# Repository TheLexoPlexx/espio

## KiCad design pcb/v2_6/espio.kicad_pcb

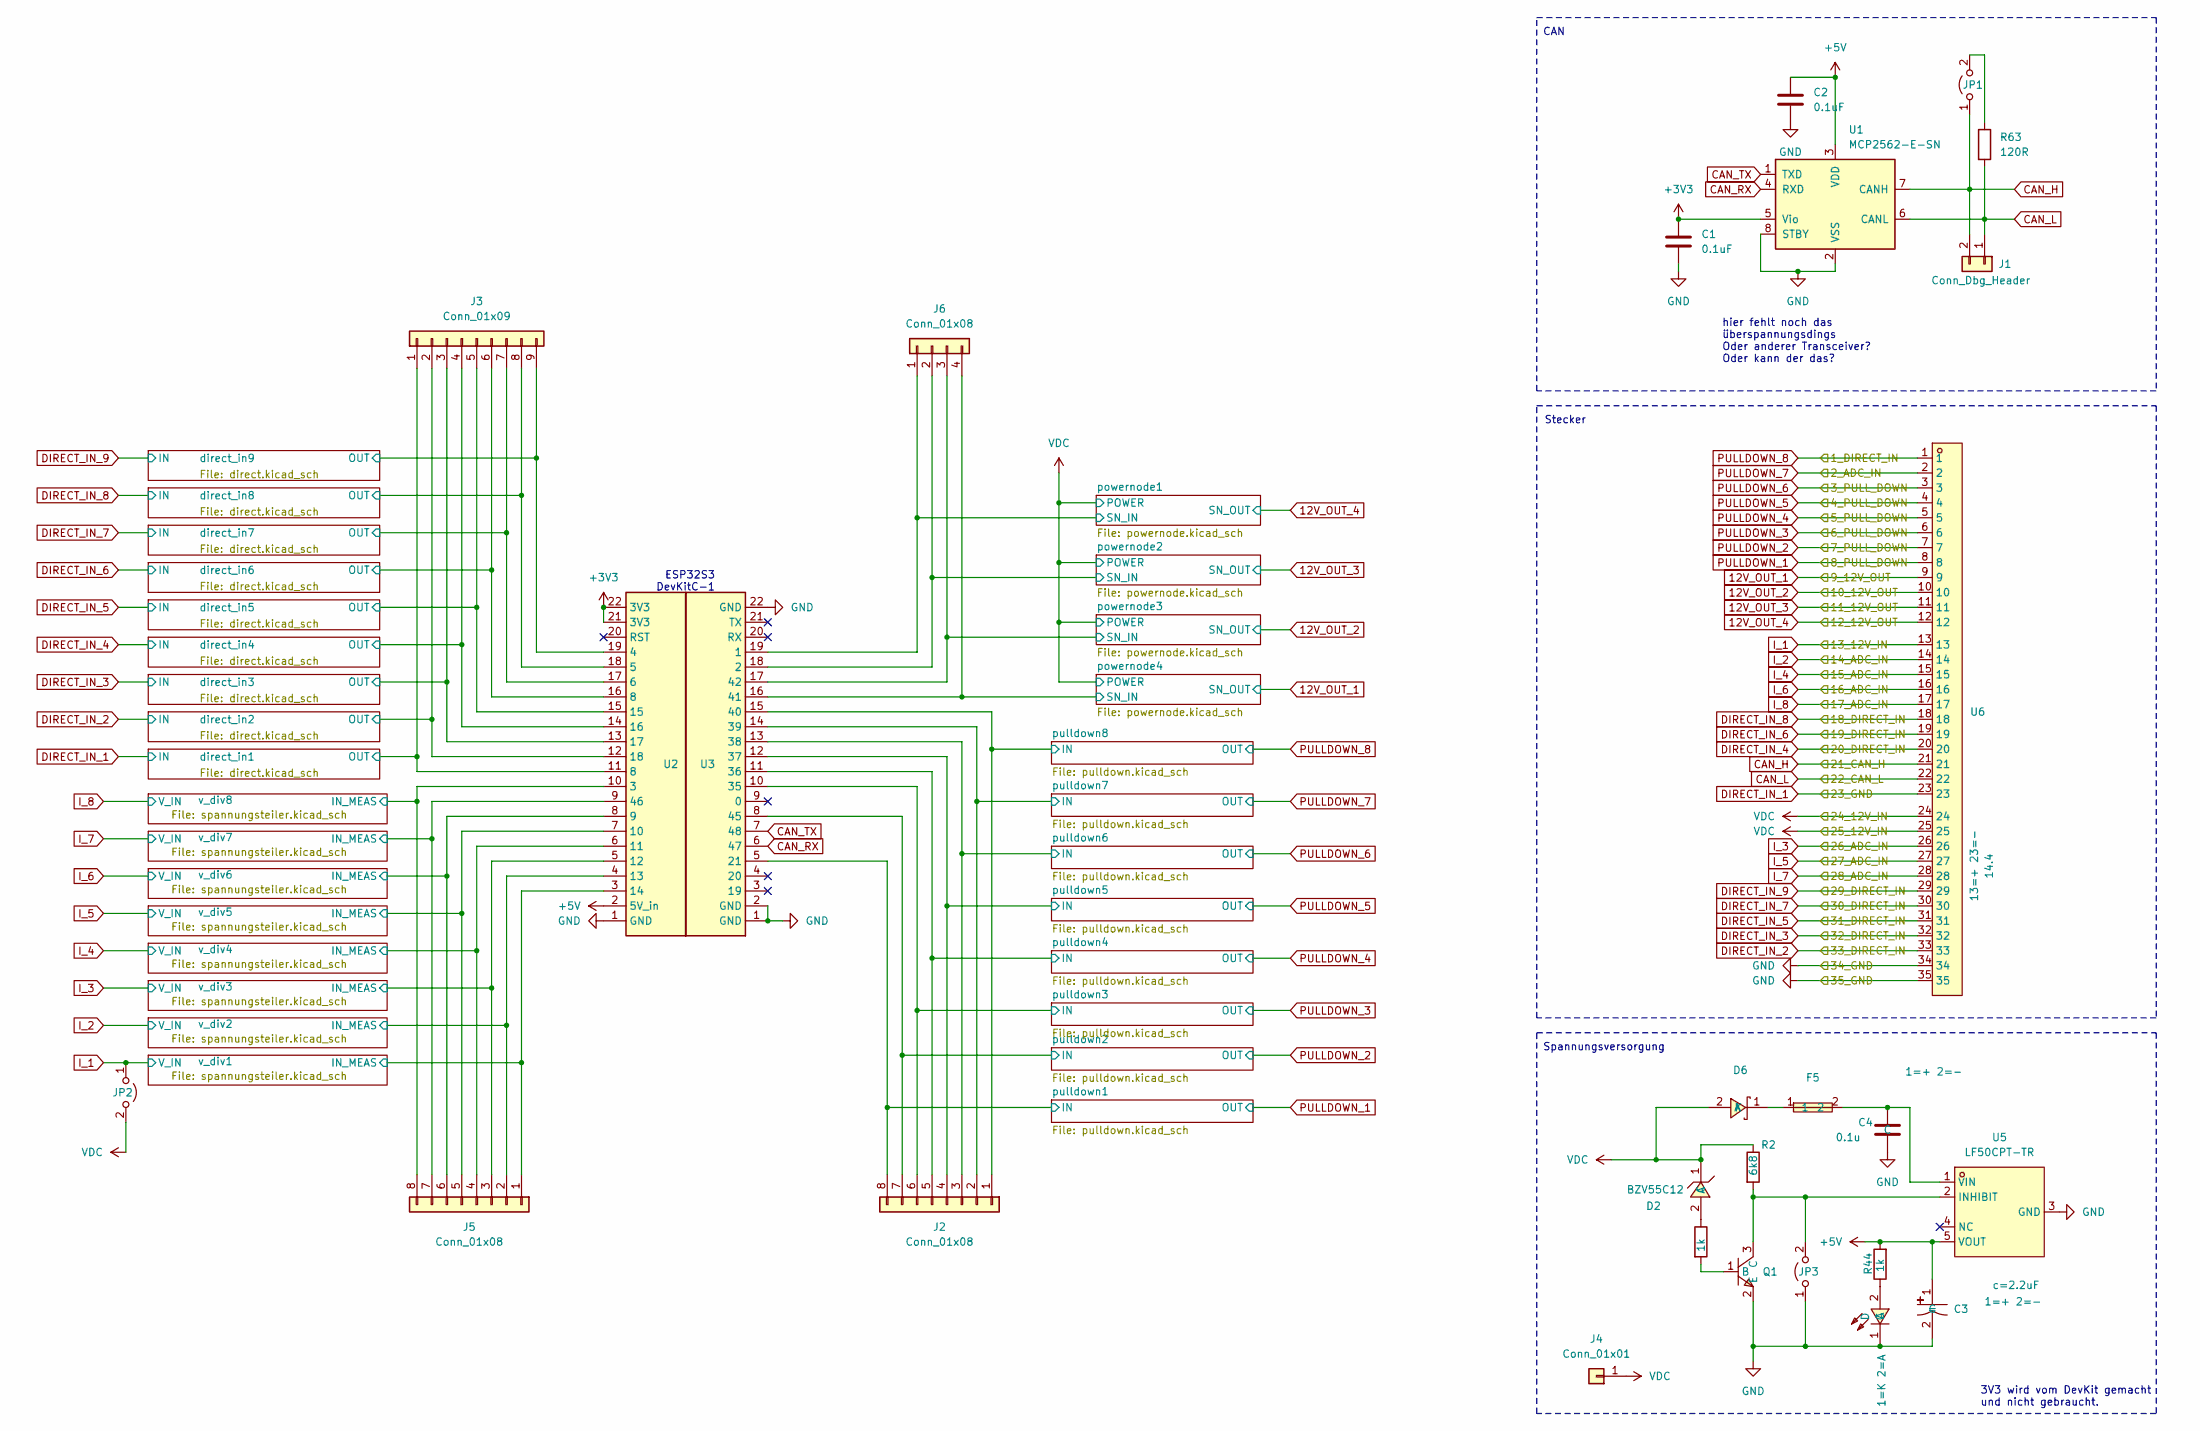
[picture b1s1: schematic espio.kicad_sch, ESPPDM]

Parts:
C1, C2: 0.1uF; C_0603_1608Metric
C3: c=2.2uF; CAP-SMD_BD6.3-L6.6-W6.6-FD; LCSC Part C335981
C4: 0.1u; C_0603_1608Metric
D2: BZV55C12; SOD-80_L3.5-W1.5-RD; LCSC Part C545360
D6: 1N5819HW-7-F; SOD-123_L2.7-W1.6-LS3.7-RD; LCSC Part C82544
F5: 1812L050/30PR; F1812; LCSC Part C151168
J1: Conn_Dbg_Header; PinHeader_1x02_P2.54mm_Vertical
J2, J5: Conn_01x08; PinHeader_1x08_P2.54mm_Vertical
J3: Conn_01x09; PinHeader_1x09_P2.54mm_Vertical
J4: Conn_01x01; PinHeader_1x01_P2.54mm_Vertical
J6: Conn_01x08; PinHeader_1x04_P2.54mm_Vertical
JP1, JP3: Jumper_2_Open; SolderJumper-2_P1.3mm_Open_Pad1.0x1.5mm
JP2: VCC_as_Pin_8; SolderJumper-2_P1.3mm_Open_Pad1.0x1.5mm
LED1: ${SIM.PARAMS}; LED0603-RD; LCSC Part C193191
Q1: 2SC1623 300-400; SOT-23-3_L2.9-W1.3-P1.90-LS2.4-BR; LCSC Part C2133
R2: 6k8; R_0603_1608Metric
R3, R44: 1k; R_0603_1608Metric
R63: 120R; R_0603_1608Metric
U1: MCP2562-E-SN; SOIC-8_3.9x4.9mm_P1.27mm; lcsc C53609
U2, U3: PinSocket_1x22_P2.54mm_Vertical
U5: LF50CPT-TR; PPAK-5_L6.5-W6.1-P1.27-LS10.0-TL; LCSC Part C2970955
U6: 14.4; CONN-TH_35P-P4.00_K776180WR-2; LCSC Part C2997462

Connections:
12V_OUT_1: U6.9; also elsewhere on the board
12V_OUT_2: U6.10; also elsewhere on the board
12V_OUT_3: U6.11; also elsewhere on the board
12V_OUT_4: U6.12; also elsewhere on the board
+3V3: C1.1, U1.5 (Vio), U2.21 (3V3), U2.22 (3V3)
+5V: C2.1, C3.1, R44.2, U1.3 (VDD), U2.2 (5V_in), U5.5 (VOUT)
/powernode1/SN_IN: J6.1, U3.19 (1); also elsewhere on the board
/powernode2/SN_IN: J6.2, U3.18 (2); also elsewhere on the board
/powernode3/SN_IN: J6.3, U3.17 (42); also elsewhere on the board
/powernode4/SN_IN: J6.4, U3.16 (41); also elsewhere on the board
/pulldown1/IN: J2.8, U3.5 (21); also elsewhere on the board
/pulldown2/IN: J2.7, U3.8 (45); also elsewhere on the board
/pulldown3/IN: J2.6, U3.10 (35); also elsewhere on the board
/pulldown4/IN: J2.5, U3.11 (36); also elsewhere on the board
/pulldown5/IN: J2.4, U3.12 (37); also elsewhere on the board
/pulldown6/IN: J2.3, U3.13 (38); also elsewhere on the board
/pulldown7/IN: J2.2, U3.14 (39); also elsewhere on the board
/pulldown8/IN: J2.1, U3.15 (40); also elsewhere on the board
/v_div1/IN_MEAS: J5.1, U2.3 (14); also elsewhere on the board
/v_div2/IN_MEAS: J5.2, U2.4 (13); also elsewhere on the board
/v_div3/IN_MEAS: J5.3, U2.5 (12); also elsewhere on the board
/v_div4/IN_MEAS: J5.4, U2.6 (11); also elsewhere on the board
/v_div5/IN_MEAS: J5.5, U2.7 (10); also elsewhere on the board
/v_div6/IN_MEAS: J5.6, U2.8 (9); also elsewhere on the board
/v_div7/IN_MEAS: J5.7, U2.9 (46); also elsewhere on the board
/v_div8/IN_MEAS: J5.8, U2.10 (3); also elsewhere on the board
CAN_H: J1.2, JP1.1 (A), U1.7 (CANH), U6.21
CAN_L: J1.1, R63.2, U1.6 (CANL), U6.22
CAN_RX: U1.4 (RXD), U3.6 (47)
CAN_TX: U1.1 (TXD), U3.7 (48)
DIRECT_IN_1: J3.1, U2.11 (8), U6.23; also elsewhere on the board
DIRECT_IN_2: J3.2, U2.12 (18), U6.33; also elsewhere on the board
DIRECT_IN_3: J3.3, U2.13 (17), U6.32; also elsewhere on the board
DIRECT_IN_4: J3.4, U2.14 (16), U6.20; also elsewhere on the board
DIRECT_IN_5: J3.5, U2.15, U6.31; also elsewhere on the board
DIRECT_IN_6: J3.6, U2.16 (8), U6.19; also elsewhere on the board
DIRECT_IN_7: J3.7, U2.17 (6), U6.30; also elsewhere on the board
DIRECT_IN_8: J3.8, U2.18 (5), U6.18; also elsewhere on the board
DIRECT_IN_9: J3.9, U2.19 (4), U6.29; also elsewhere on the board
GND: C1.2, C2.2, C3.2, C4.2, JP3.1 (A), LED1.1 (C), Q1.2 (E), U1.2 (VSS), U1.8 (STBY), U2.1 (GND), U3.1 (GND), U3.2 (GND), U3.22 (GND), U5.3 (GND), U6.34, U6.35; also elsewhere on the board
I_1: JP2.1 (A), U6.13; also elsewhere on the board
I_2: U6.14; also elsewhere on the board
I_3: U6.26; also elsewhere on the board
I_4: U6.15; also elsewhere on the board
I_5: U6.27; also elsewhere on the board
I_6: U6.16; also elsewhere on the board
I_7: U6.28; also elsewhere on the board
I_8: U6.17; also elsewhere on the board
unnamed: D2.2 (A), R3.1
unnamed: D6.1 (K), F5.1
unnamed: JP1.2 (B), R63.1
unnamed: JP3.2 (B), Q1.3 (C), R2.2, U5.2 (INHIBIT)
unnamed: LED1.2 (A), R44.1
unnamed: Q1.1 (B), R3.2
unnamed: C4.1, F5.2, U5.1 (VIN)
PULLDOWN_1: U6.8; also elsewhere on the board
PULLDOWN_2: U6.7; also elsewhere on the board
PULLDOWN_3: U6.6; also elsewhere on the board
PULLDOWN_4: U6.5; also elsewhere on the board
PULLDOWN_5: U6.4; also elsewhere on the board
PULLDOWN_6: U6.3; also elsewhere on the board
PULLDOWN_7: U6.2; also elsewhere on the board
PULLDOWN_8: U6.1; also elsewhere on the board
VDC: D2.1 (C), D6.2 (A), J4.1, JP2.2 (B), R2.1, U6.24, U6.25; also elsewhere on the board

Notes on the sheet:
3V3 wird vom DevKit gemacht und nicht gebraucht.
Stecker
CAN
hier fehlt noch das überspannungsdings Oder anderer Transceiver? Oder kann der das?
Spannungsversorgung
ESP32S3 DevKitC-1

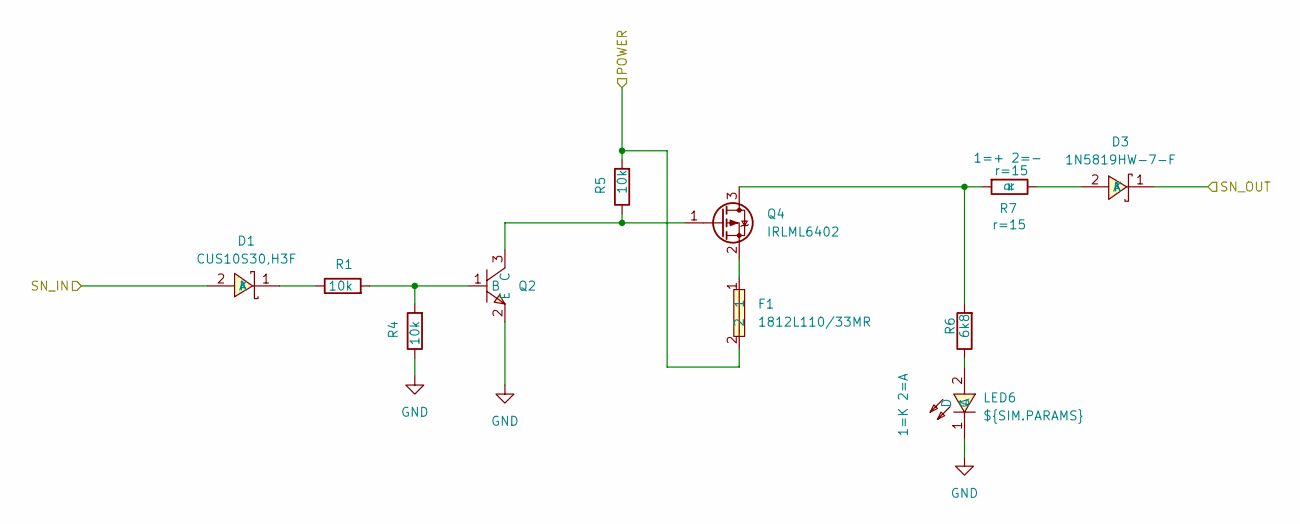
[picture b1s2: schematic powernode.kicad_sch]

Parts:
D1: CUS10S30,H3F; SOD-323_L1.8-W1.3-LS2.5-RD; LCSC Part C146335
D3: 1N5819HW-7-F; SOD-123_L2.7-W1.6-LS3.7-RD; LCSC Part C82544
F1: 1812L110/33MR; F1812; LCSC Part C142747
LED6: ${SIM.PARAMS}; LED0603-RD; LCSC Part C193191
Q2: 2SC1623 300-400; SOT-23-3_L2.9-W1.3-P1.90-LS2.4-BR; LCSC Part C2133
Q4: IRLML6402; SOT-23
R1, R4, R5: 10k; R_0603_1608Metric
R6: 6k8; R_0603_1608Metric
R7: r=15; R_Axial_DIN0207_L6.3mm_D2.5mm_P7.62mm_Horizontal

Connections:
12V_OUT_4: D3.1 (K); also elsewhere on the board
/powernode1/SN_IN: D1.2 (A); also elsewhere on the board
GND: LED6.1 (C), Q2.2 (E), R4.1; also elsewhere on the board
unnamed: D1.1 (K), R1.1
unnamed: D3.2 (A), R7.1
unnamed: LED6.2 (A), R6.1
unnamed: Q2.1 (B), R1.2, R4.2
unnamed: Q2.3 (C), Q4.1 (G), R5.1
unnamed: Q4.3 (D), R6.2, R7.2
unnamed: F1.1, Q4.2 (S)
VDC: F1.2, R5.2; also elsewhere on the board

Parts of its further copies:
D4, D7, D9: CUS10S30,H3F; SOD-323_L1.8-W1.3-LS2.5-RD; LCSC Part C146335
D5, D8, D10: 1N5819HW-7-F; SOD-123_L2.7-W1.6-LS3.7-RD; LCSC Part C82544
F2, F3, F4: 1812L110/33MR; F1812; LCSC Part C142747
Q6, Q9, Q14: 2SC1623 300-400; SOT-23-3_L2.9-W1.3-P1.90-LS2.4-BR; LCSC Part C2133
Q8, Q11, Q15: IRLML6402; SOT-23
R8, R9, R10, R16, R18, R19, R30, R31, R32: 10k; R_0603_1608Metric
R11, R20, R37: 6k8; R_0603_1608Metric
R13, R29, R38: r=15; R_Axial_DIN0207_L6.3mm_D2.5mm_P7.62mm_Horizontal

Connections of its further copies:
12V_OUT_1: D10.1 (K); also elsewhere on the board
12V_OUT_2: D8.1 (K); also elsewhere on the board
12V_OUT_3: D5.1 (K); also elsewhere on the board
/powernode2/SN_IN: D4.2 (A); also elsewhere on the board
/powernode3/SN_IN: D7.2 (A); also elsewhere on the board
/powernode4/SN_IN: D9.2 (A); also elsewhere on the board
GND: Q6.2 (E), Q9.2 (E), Q14.2 (E), R9.1, R18.1, R31.1; also elsewhere on the board
unnamed: D4.1 (K), R8.1
unnamed: D5.2 (A), R13.1
unnamed: D7.1 (K), R16.1
unnamed: D8.2 (A), R29.1
unnamed: D9.1 (K), R30.1
unnamed: D10.2 (A), R38.1
unnamed 75: R11.1; also elsewhere on the board
unnamed 76: R20.1; also elsewhere on the board
unnamed 77: R37.1; also elsewhere on the board
unnamed: Q6.1 (B), R8.2, R9.2
unnamed: Q6.3 (C), Q8.1 (G), R10.1
unnamed: Q8.3 (D), R11.2, R13.2
unnamed: F2.1, Q8.2 (S)
unnamed: Q9.1 (B), R16.2, R18.2
unnamed: Q11.3 (D), R20.2, R29.2
unnamed: Q9.3 (C), Q11.1 (G), R19.1
unnamed: F3.1, Q11.2 (S)
unnamed: Q14.1 (B), R30.2, R31.2
unnamed: Q14.3 (C), Q15.1 (G), R32.1
unnamed: Q15.3 (D), R37.2, R38.2
unnamed: F4.1, Q15.2 (S)
VDC: F2.2, F3.2, F4.2, R10.2, R19.2, R32.2; also elsewhere on the board

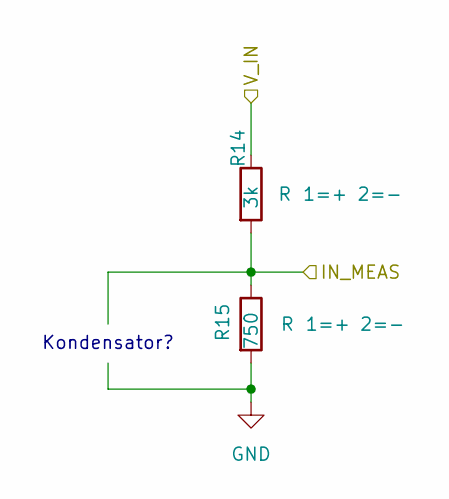
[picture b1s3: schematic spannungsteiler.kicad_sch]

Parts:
R14: 3k; R_0603_1608Metric
R15: 750; R_0603_1608Metric

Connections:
/v_div1/IN_MEAS: R14.2, R15.1; also elsewhere on the board
GND: R15.2; also elsewhere on the board
I_1: R14.1; also elsewhere on the board

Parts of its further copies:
R12, R21, R23, R25, R27, R33, R35: 3k; R_0603_1608Metric
R17, R22, R24, R26, R28, R34, R36: 750; R_0603_1608Metric

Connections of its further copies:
/v_div2/IN_MEAS: R12.2, R17.1; also elsewhere on the board
/v_div3/IN_MEAS: R21.2, R22.1; also elsewhere on the board
/v_div4/IN_MEAS: R23.2, R24.1; also elsewhere on the board
/v_div5/IN_MEAS: R25.2, R26.1; also elsewhere on the board
/v_div6/IN_MEAS: R27.2, R28.1; also elsewhere on the board
/v_div7/IN_MEAS: R33.2, R34.1; also elsewhere on the board
/v_div8/IN_MEAS: R35.2, R36.1; also elsewhere on the board
GND: R17.2, R22.2, R24.2, R26.2, R28.2, R34.2, R36.2; also elsewhere on the board
I_2: R12.1; also elsewhere on the board
I_3: R21.1; also elsewhere on the board
I_4: R23.1; also elsewhere on the board
I_5: R25.1; also elsewhere on the board
I_6: R27.1; also elsewhere on the board
I_7: R33.1; also elsewhere on the board
I_8: R35.1; also elsewhere on the board

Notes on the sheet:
Kondensator?

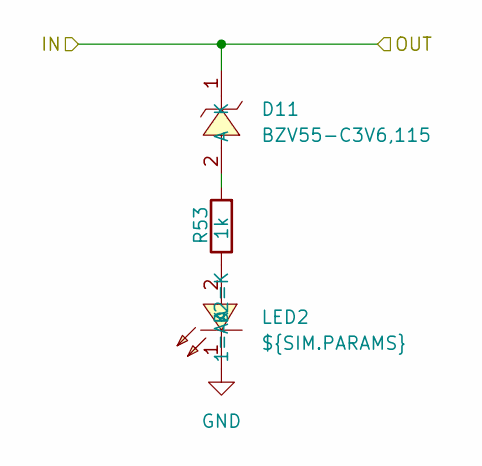
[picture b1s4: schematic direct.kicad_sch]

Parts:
D11: BZV55-C3V6,115; LL-34_L3.5-W1.5-RD; LCSC Part C513232
LED2: ${SIM.PARAMS}; LED0603-RD; LCSC Part C205445
R53: 1k; R_0603_1608Metric

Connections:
DIRECT_IN_1: D11.1 (K); also elsewhere on the board
GND: LED2.1 (K); also elsewhere on the board
unnamed: D11.2 (A), R53.2
unnamed: LED2.2 (A), R53.1

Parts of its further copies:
D12, D13, D14, D15, D16, D17, D18, D19: BZV55-C3V6,115; LL-34_L3.5-W1.5-RD; LCSC Part C513232
R54, R55, R56, R57, R58, R59, R60, R61: 1k; R_0603_1608Metric

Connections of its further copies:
DIRECT_IN_2: D12.1 (K); also elsewhere on the board
DIRECT_IN_3: D13.1 (K); also elsewhere on the board
DIRECT_IN_4: D14.1 (K); also elsewhere on the board
DIRECT_IN_5: D15.1 (K); also elsewhere on the board
DIRECT_IN_6: D16.1 (K); also elsewhere on the board
DIRECT_IN_7: D17.1 (K); also elsewhere on the board
DIRECT_IN_8: D18.1 (K); also elsewhere on the board
DIRECT_IN_9: D19.1 (K); also elsewhere on the board
unnamed: D12.2 (A), R54.2
unnamed: D13.2 (A), R55.2
unnamed: D14.2 (A), R56.2
unnamed: D15.2 (A), R57.2
unnamed: D16.2 (A), R58.2
unnamed: D17.2 (A), R59.2
unnamed: D18.2 (A), R60.2
unnamed: D19.2 (A), R61.2
unnamed 71: R54.1; also elsewhere on the board
unnamed 72: R55.1; also elsewhere on the board
unnamed 73: R56.1; also elsewhere on the board
unnamed 78: R57.1; also elsewhere on the board
unnamed 79: R58.1; also elsewhere on the board
unnamed 80: R59.1; also elsewhere on the board
unnamed 81: R60.1; also elsewhere on the board
unnamed 82: R61.1; also elsewhere on the board

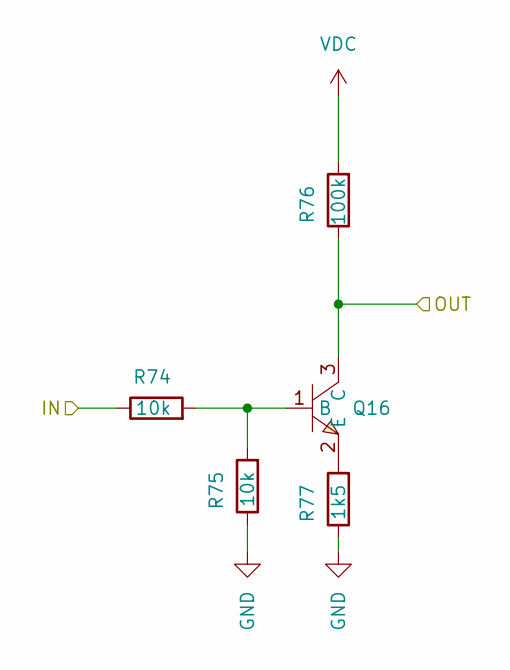
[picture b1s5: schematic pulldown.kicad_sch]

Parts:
Q16: 2SC1623 300-400; SOT-23-3_L2.9-W1.3-P1.90-LS2.4-BR; LCSC Part C2133
R74, R75: 10k; R_0603_1608Metric
R76: 100k; R_0603_1608Metric
R77: 1k5; R_0603_1608Metric

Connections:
/pulldown7/IN: R74.1; also elsewhere on the board
GND: R75.1, R77.1; also elsewhere on the board
unnamed: Q16.1 (B), R74.2, R75.2
unnamed: Q16.2 (E), R77.2
PULLDOWN_7: Q16.3 (C), R76.1; also elsewhere on the board
VDC: R76.2; also elsewhere on the board

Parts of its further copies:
Q3, Q5, Q7, Q10, Q12, Q13, Q17: 2SC1623 300-400; SOT-23-3_L2.9-W1.3-P1.90-LS2.4-BR; LCSC Part C2133
R39, R42, R45, R48, R49, R51, R80: 100k; R_0603_1608Metric
R40, R43, R46, R47, R50, R62, R66, R69, R70, R71, R72, R73, R78, R79: 10k; R_0603_1608Metric
R41, R52, R64, R65, R67, R68, R81: 1k5; R_0603_1608Metric

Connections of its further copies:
/pulldown1/IN: R46.1; also elsewhere on the board
/pulldown2/IN: R69.1; also elsewhere on the board
/pulldown3/IN: R70.1; also elsewhere on the board
/pulldown4/IN: R71.1; also elsewhere on the board
/pulldown5/IN: R72.1; also elsewhere on the board
/pulldown6/IN: R73.1; also elsewhere on the board
/pulldown8/IN: R78.1; also elsewhere on the board
GND: R40.1, R41.1, R43.1, R47.1, R50.1, R52.1, R62.1, R64.1, R65.1, R66.1, R67.1, R68.1, R79.1, R81.1; also elsewhere on the board
unnamed: Q3.1 (B), R40.2, R46.2
unnamed: Q3.2 (E), R41.2
unnamed: Q5.1 (B), R43.2, R69.2
unnamed: Q5.2 (E), R52.2
unnamed: Q7.1 (B), R47.2, R70.2
unnamed: Q7.2 (E), R64.2
unnamed: Q10.1 (B), R50.2, R71.2
unnamed: Q10.2 (E), R65.2
unnamed: Q12.1 (B), R62.2, R72.2
unnamed: Q12.2 (E), R67.2
unnamed: Q13.1 (B), R66.2, R73.2
unnamed: Q13.2 (E), R68.2
unnamed: Q17.1 (B), R78.2, R79.2
unnamed: Q17.2 (E), R81.2
PULLDOWN_1: Q3.3 (C), R39.1; also elsewhere on the board
PULLDOWN_2: Q5.3 (C), R42.1; also elsewhere on the board
PULLDOWN_3: Q7.3 (C), R45.1; also elsewhere on the board
PULLDOWN_4: Q10.3 (C), R48.1; also elsewhere on the board
PULLDOWN_5: Q12.3 (C), R49.1; also elsewhere on the board
PULLDOWN_6: Q13.3 (C), R51.1; also elsewhere on the board
PULLDOWN_8: Q17.3 (C), R80.1; also elsewhere on the board
VDC: R39.2, R42.2, R45.2, R48.2, R49.2, R51.2, R80.2; also elsewhere on the board

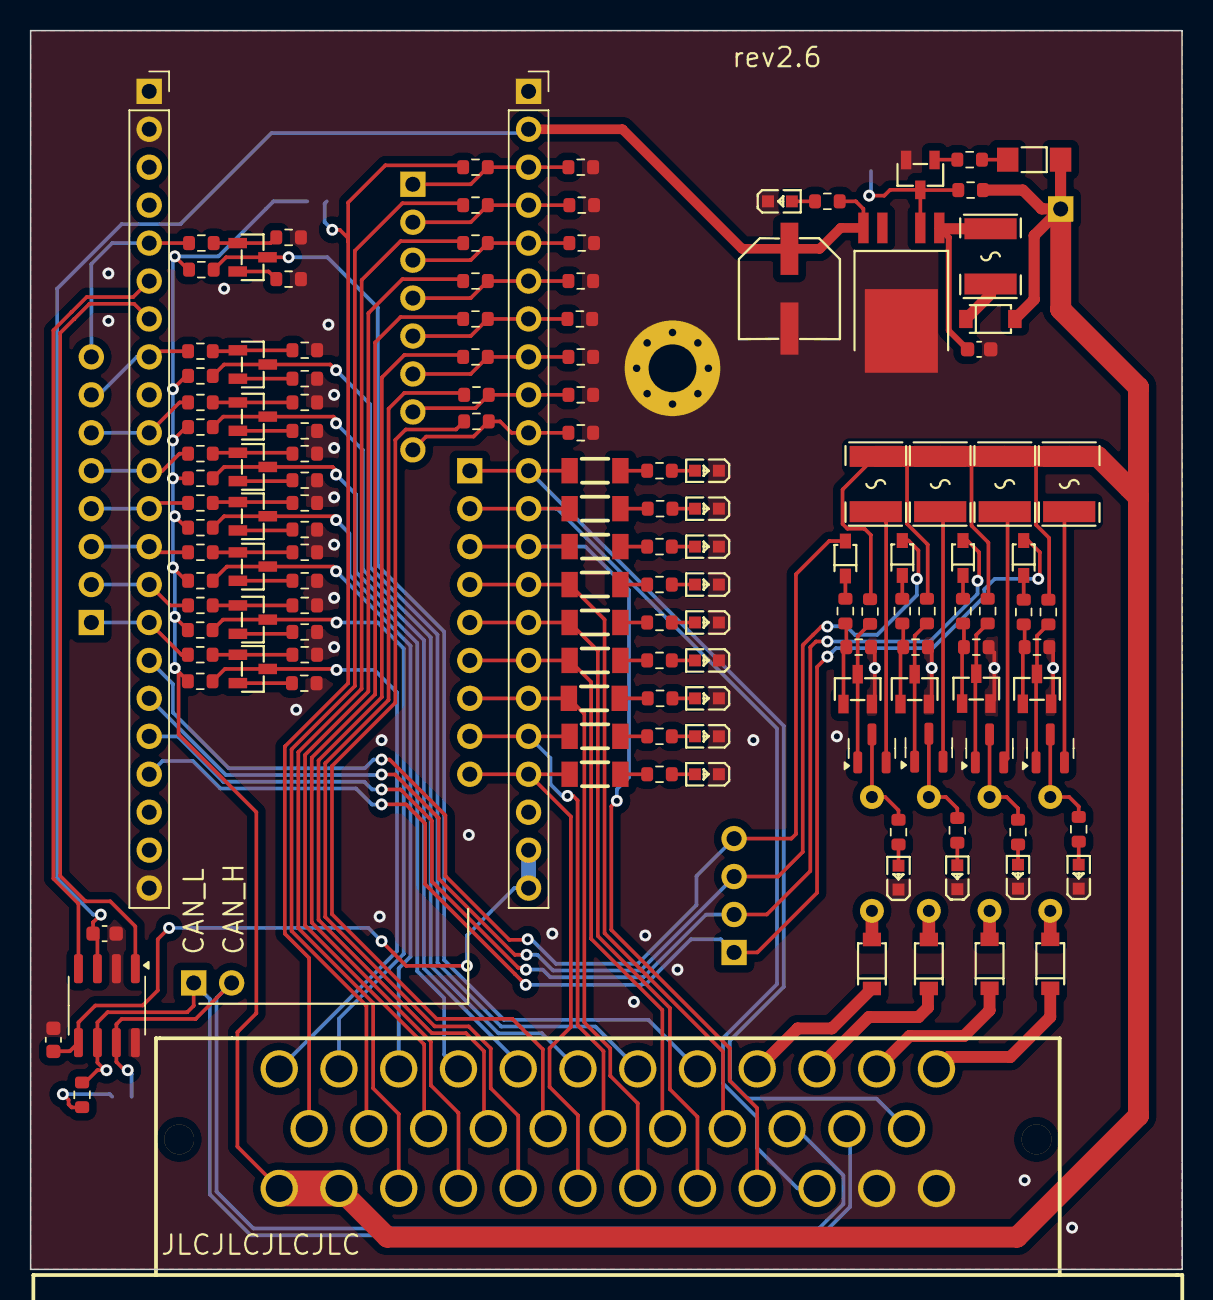
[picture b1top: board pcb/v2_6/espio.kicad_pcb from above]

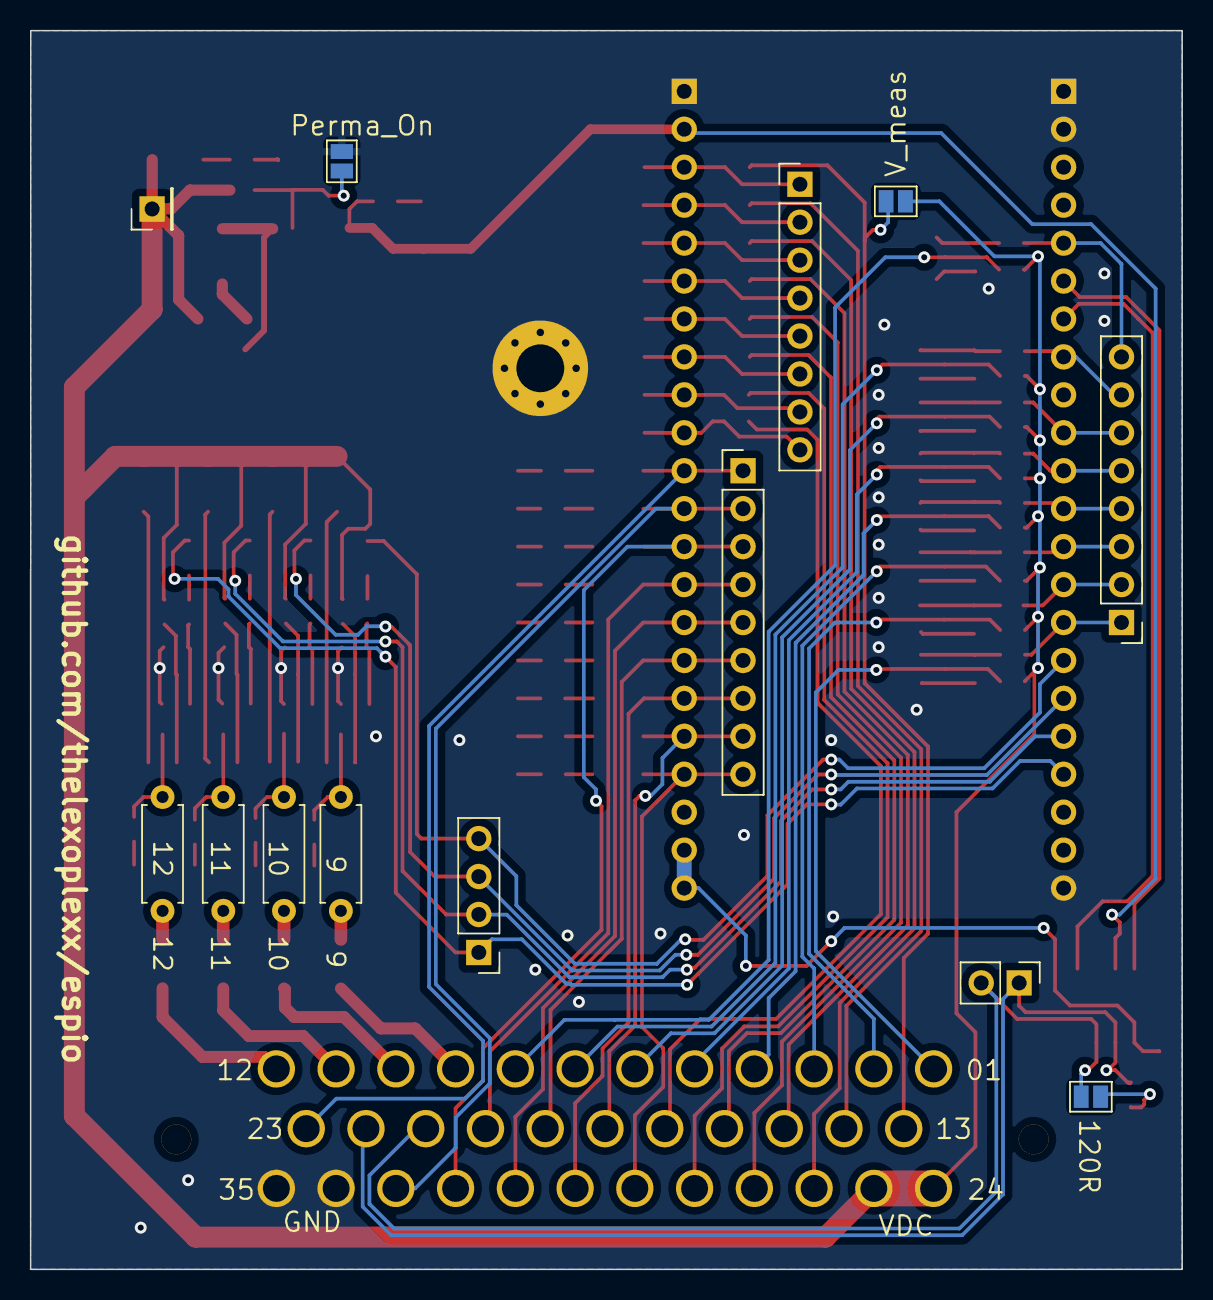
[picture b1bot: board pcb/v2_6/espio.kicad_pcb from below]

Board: 2 copper layers, 77.1 x 82.9 mm, 154 parts (13 on the bottom side), 126 nets.

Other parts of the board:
LED3, LED4, LED5, LED7, LED8, LED9, LED10, LED11, LED12, LED13, LED14: LED0603-RD

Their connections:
GND: LED3.1 (K), LED4.1 (K), LED5.1 (K), LED7.1 (C), LED8.1 (C), LED9.1 (C), LED10.1 (K), LED11.1 (K), LED12.1 (K), LED13.1 (K), LED14.1 (K); also elsewhere on the board
unnamed 71: LED3.2 (A); also elsewhere on the board
unnamed 72: LED4.2 (A); also elsewhere on the board
unnamed 73: LED5.2 (A); also elsewhere on the board
unnamed 75: LED7.2 (A); also elsewhere on the board
unnamed 76: LED8.2 (A); also elsewhere on the board
unnamed 77: LED9.2 (A); also elsewhere on the board
unnamed 78: LED10.2 (A); also elsewhere on the board
unnamed 79: LED11.2 (A); also elsewhere on the board
unnamed 80: LED12.2 (A); also elsewhere on the board
unnamed 81: LED13.2 (A); also elsewhere on the board
unnamed 82: LED14.2 (A); also elsewhere on the board

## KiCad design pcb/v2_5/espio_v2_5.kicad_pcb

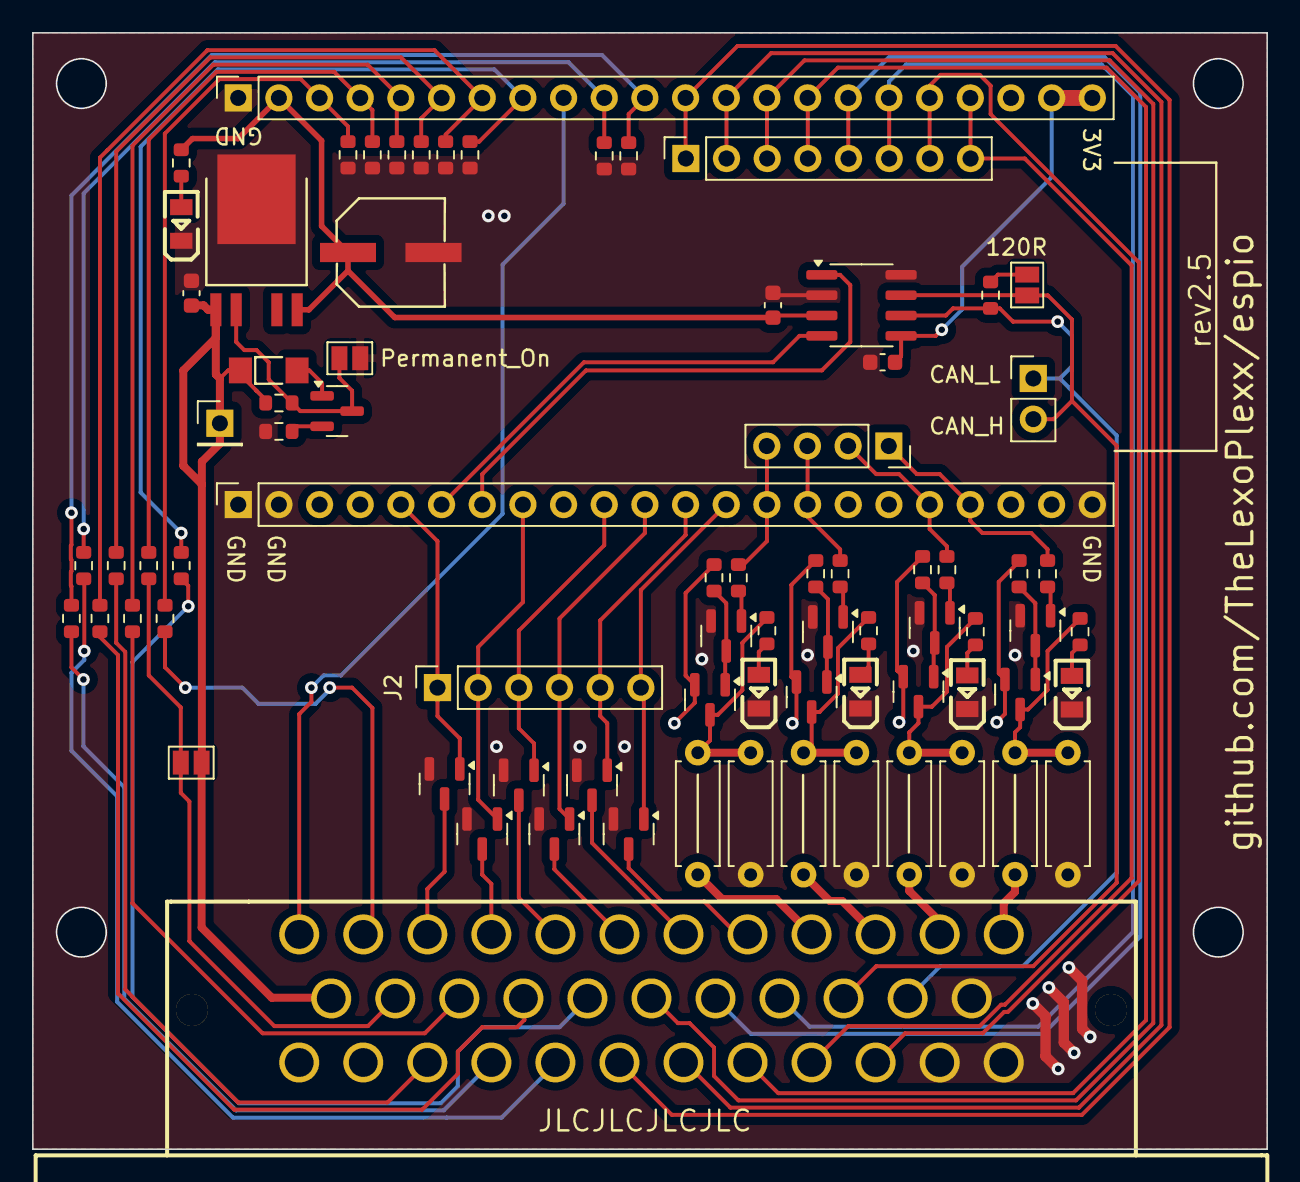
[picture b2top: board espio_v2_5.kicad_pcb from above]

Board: 2 copper layers, 77.1 x 69.7 mm, 78 parts (0 on the bottom side), 74 nets.

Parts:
C1, C2, C4: 0.1uF; C_0603_1608Metric
C3: RVT2A2R2M0605_C335981; CAP-SMD_BD6.3-L6.6-W6.6-FD
D2: BZV55C15_C545332; SOD-80_L3.5-W1.5-RD
J1: Conn_Dbg_Header; PinHeader_1x02_P2.54mm_Vertical
J2: Conn_01x07; PinSocket_1x06_P2.54mm_Vertical
J3: Conn_01x08; PinSocket_1x08_P2.54mm_Vertical
J4: Conn_01x01; PinHeader_1x01_P2.54mm_Vertical
J6: Conn_01x08; PinSocket_1x04_P2.54mm_Vertical
JP1, JP3: Jumper_2_Open; SolderJumper-2_P1.3mm_Open_Pad1.0x1.5mm
JP2: VCC_as_Pin_8; SolderJumper-2_P1.3mm_Open_Pad1.0x1.5mm
LED1, LED2, LED3, LED4, LED5: 0805G (Green); LED0805-R-RD
Q1, Q3, Q5, Q7, Q9, Q10, Q11, Q12, Q13, Q15, Q16: BC817; SOT-23
Q2, Q4, Q6, Q8: IRLML6402; SOT-23
R1, R3, R18, R19, R20: 1k; R_0603_1608Metric
R2: 4k; R_0603_1608Metric
R4, R5, R6, R7, R8, R9, R10, R11: DNP; R_Axial_DIN0207_L6.3mm_D2.5mm_P7.62mm_Horizontal
R12, R14, R21, R23, R25, R27, R33, R35: 3k; R_0603_1608Metric
R13, R16, R37, R38: 2k4; R_0603_1608Metric
R15, R17, R22, R24, R26, R28, R34, R36: 750R; R_0603_1608Metric
R29, R30, R31, R32: 10k; R_0603_1608Metric
R39: 470; R_0603_1608Metric
R63: 120R; R_0603_1608Metric
U1: MCP2562-E-SN; SOIC-8_3.9x4.9mm_P1.27mm
U2, U3: PinSocket_1x22_P2.54mm_Vertical
U5: LF50CPT-TR; PPAK-5_L6.5-W6.1-P1.27-LS10.0-TL
U6: K776180WR-1; CONN-TH_35P-P4.00_K776180WR-2

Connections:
+3V3: C1.1, U1.5 (Vio), U2.21 (3V3), U2.22 (3V3)
+5V: C2.1, C3.1, R39.1, U1.3 (VDD), U2.2 (5V_in), U5.5 (VOUT)
+12V: C4.1, D2.1 (C), J4.1, JP2.1 (A), Q2.2 (S), Q4.2 (S), Q6.2 (S), Q8.2 (S), R2.1, R29.2, R30.2, R31.2, R32.2, U5.1 (VIN), U6.13, U6.24, U6.25
/3_PULL_DOWN: Q13.3 (C), U6.3
/4_PULL_DOWN: Q12.3 (C), U6.4
/5_PULL_DOWN: Q15.3 (C), U6.5
/6_PULL_DOWN: Q10.3 (C), U6.6
/7_PULL_DOWN: Q9.3 (C), U6.7
/8_PULL_DOWN: Q11.3 (C), U6.8
/9_12V_OUT: R11.1, U6.9
/10_12V_OUT: R10.1, U6.10
/11_12V_OUT: R9.1, U6.11
/12_12V_OUT: R8.1, U6.12
/Spannungsteiler1/IN_MEAS: R21.2, R22.1, U2.4 (13)
/Spannungsteiler2/IN_MEAS: R12.2, R17.1, U2.6 (11)
/Spannungsteiler3/IN_MEAS: R23.2, R24.1, U2.5 (12)
/Spannungsteiler4/IN_MEAS: R25.2, R26.1, U2.7 (10)
/Spannungsteiler5/IN_MEAS: R27.2, R28.1, U2.8 (9)
/Spannungsteiler6/IN_MEAS: R33.2, R34.1, U2.11 (8)
/Spannungsteiler7/IN_MEAS: R35.2, R36.1, U2.10 (3)
/Spannungsteiler8/IN_MEAS: R14.2, R15.1, U2.3 (14)
/SwitchingNode1/SN_IN: J6.1, R1.1, U3.19 (1)
/SwitchingNode2/SN_IN: J6.2, R18.1, U3.18 (2)
/SwitchingNode3/SN_IN: J6.3, R19.1, U3.15 (40)
/SwitchingNode4/SN_IN: J6.4, R20.1, U3.14 (39)
ABS_INPUT_HL_1: J3.5, U2.16 (8), U6.19
ABS_INPUT_HL_2: J3.3, U2.14 (16), U6.18
ABS_INPUT_HR_1: J3.2, U2.13 (17), U6.30
ABS_INPUT_HR_2: J3.1, U2.12 (18), U6.29
ABS_INPUT_VL_1: J3.8, U2.19 (4), U6.32
ABS_INPUT_VL_2: J3.7, U2.18 (5), U6.33
ABS_INPUT_VR_1: J3.6, U2.17 (6), U6.20
ABS_INPUT_VR_2: J3.4, U2.15, U6.31
CAN_H: J1.2, JP1.1 (A), U1.7 (CANH), U6.21
CAN_L: J1.1, R63.2, U1.6 (CANL), U6.22
CAN_RX: U1.4 (RXD), U3.6 (47)
CAN_TX: U1.1 (TXD), U3.7 (48)
GND: C1.2, C2.2, C3.2, C4.2, JP3.1 (A), LED1.2 (K), LED2.2 (K), LED3.2 (K), LED4.2 (K), LED5.2 (K), Q1.2 (E), Q3.2 (E), Q5.2 (E), Q7.2 (E), Q9.2 (E), Q10.2 (E), Q11.2 (E), Q12.2 (E), Q13.2 (E), Q15.2 (E), R3.2, R4.1, R5.1, R6.1, R7.1, R15.2, R17.2, R22.2, R24.2, R26.2, R28.2, R34.2, R36.2, U1.2 (VSS), U1.8 (STBY), U2.1 (GND), U3.1 (GND), U3.2 (GND), U3.22 (GND), U5.3 (GND), U6.23, U6.34, U6.35
I_1: JP2.2 (B), R21.1, U6.14
I_2: R23.1, U6.15
I_3: R25.1, U6.16
I_4: R27.1, U6.17
I_6: R14.1, U6.2
I_8: R12.1, U6.26
I_9: R33.1, U6.27
I_10: R35.1, U6.28
unnamed: D2.2 (A), Q16.1 (B)
unnamed: J2.1, Q13.1 (B), U3.5 (21)
unnamed: J2.2, Q12.1 (B), U3.8 (45)
unnamed: J2.3, Q15.1 (B), U3.10 (35)
unnamed: J2.4, Q10.1 (B), U3.11 (36)
unnamed: J2.5, Q9.1 (B), U3.12 (37)
unnamed: J2.6, Q11.1 (B), U3.13 (38)
unnamed: JP1.2 (B), R63.1
unnamed: JP3.2 (B), Q16.3 (C), R2.2, U5.2 (INHIBIT)
unnamed: LED1.1 (A), R13.1
unnamed: LED2.1 (A), R16.1
unnamed: LED3.1 (A), R37.1
unnamed: LED4.1 (A), R38.1
unnamed: LED5.1 (A), R39.2
unnamed: Q1.1 (B), R1.2
unnamed: Q1.3 (C), Q2.1 (G), R29.1
unnamed: Q2.3 (D), R4.2, R8.2, R13.2
unnamed: Q3.1 (B), R18.2
unnamed: Q3.3 (C), Q4.1 (G), R30.1
unnamed: Q4.3 (D), R5.2, R9.2, R16.2
unnamed: Q5.1 (B), R19.2
unnamed: Q5.3 (C), Q6.1 (G), R31.1
unnamed: Q6.3 (D), R6.2, R10.2, R37.2
unnamed: Q7.1 (B), R20.2
unnamed: Q7.3 (C), Q8.1 (G), R32.1
unnamed: Q8.3 (D), R7.2, R11.2, R38.2
unnamed: Q16.2 (E), R3.1
OUT_1: U2.9 (46), U6.1

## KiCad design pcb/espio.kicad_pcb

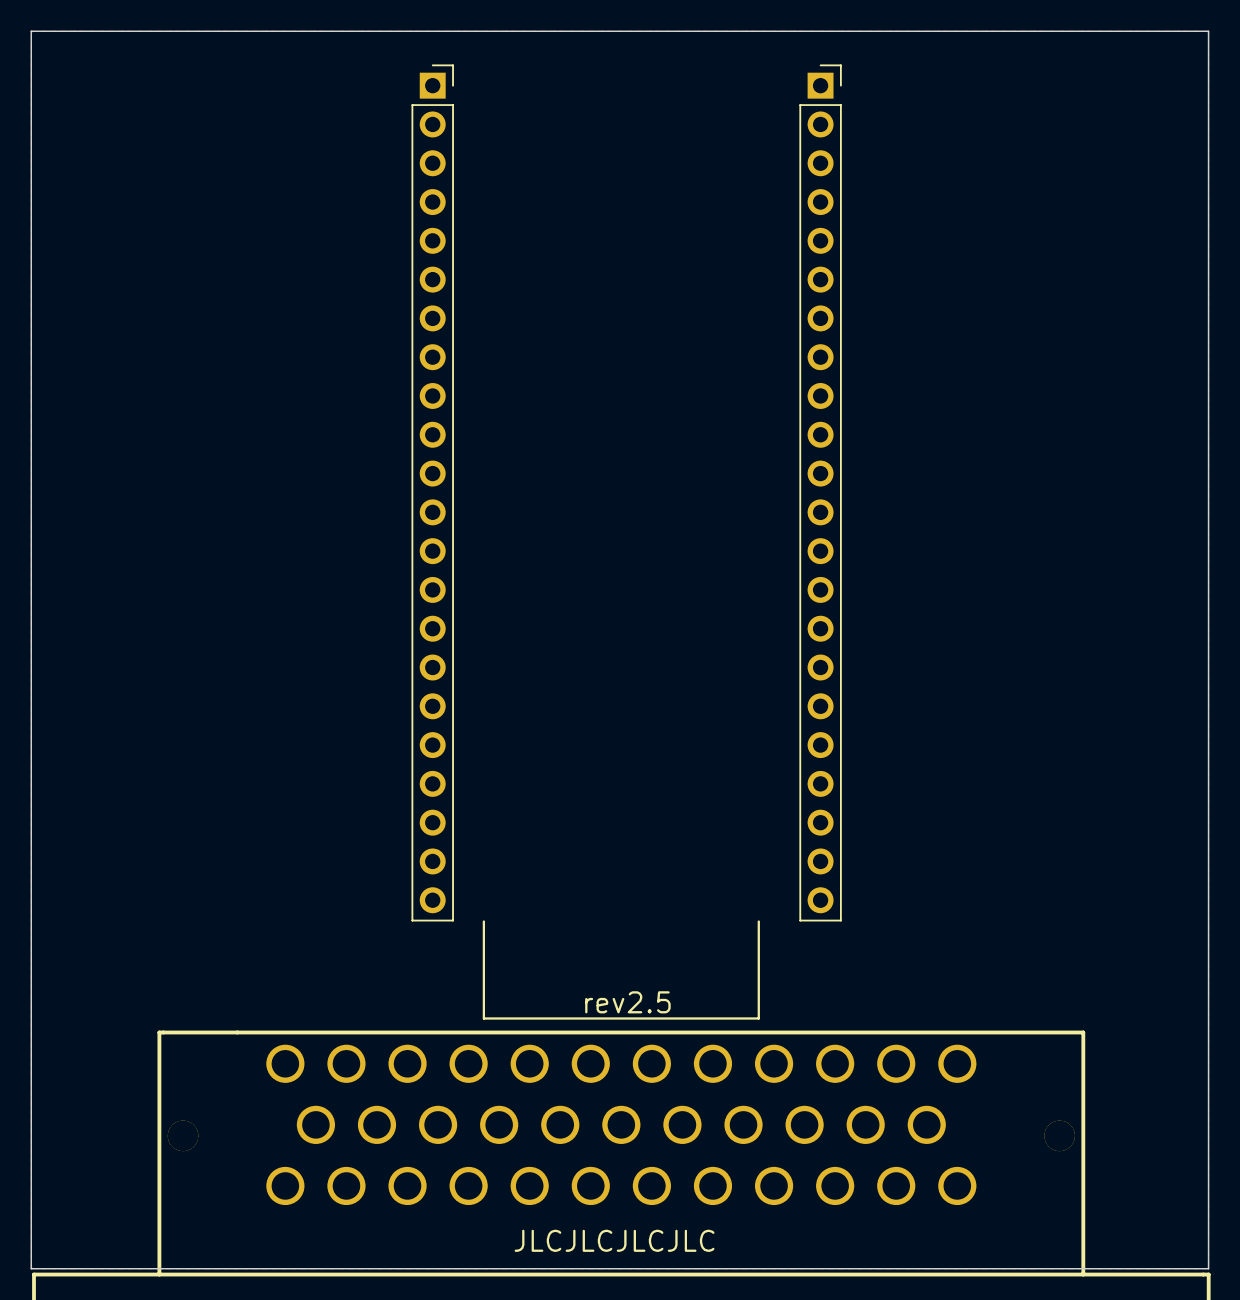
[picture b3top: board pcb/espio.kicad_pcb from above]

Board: 2 copper layers, 77.1 x 81.0 mm, 3 parts (0 on the bottom side), 12 nets, no tracks yet.

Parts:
U2, U3: PinSocket_1x22_P2.54mm_Vertical
U6: K776180WR-1; CONN-TH_35P-P4.00_K776180WR-2

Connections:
+3V3: U2.21 (3V3), U2.22 (3V3)
+12V: U6.13, U6.24, U6.25
DIRECT_IN_1: U2.11 (8), U6.1
DIRECT_IN_2: U2.12 (18), U6.33
DIRECT_IN_3: U2.13 (17), U6.32
DIRECT_IN_4: U2.14 (16), U6.31
DIRECT_IN_5: U2.15, U6.30
DIRECT_IN_6: U2.16 (8), U6.29
DIRECT_IN_7: U2.17 (6), U6.20
DIRECT_IN_8: U2.18 (5), U6.19
DIRECT_IN_9: U2.19 (4), U6.18
GND: U2.1 (GND), U3.1 (GND), U3.2 (GND), U3.22 (GND), U6.23, U6.34, U6.35
